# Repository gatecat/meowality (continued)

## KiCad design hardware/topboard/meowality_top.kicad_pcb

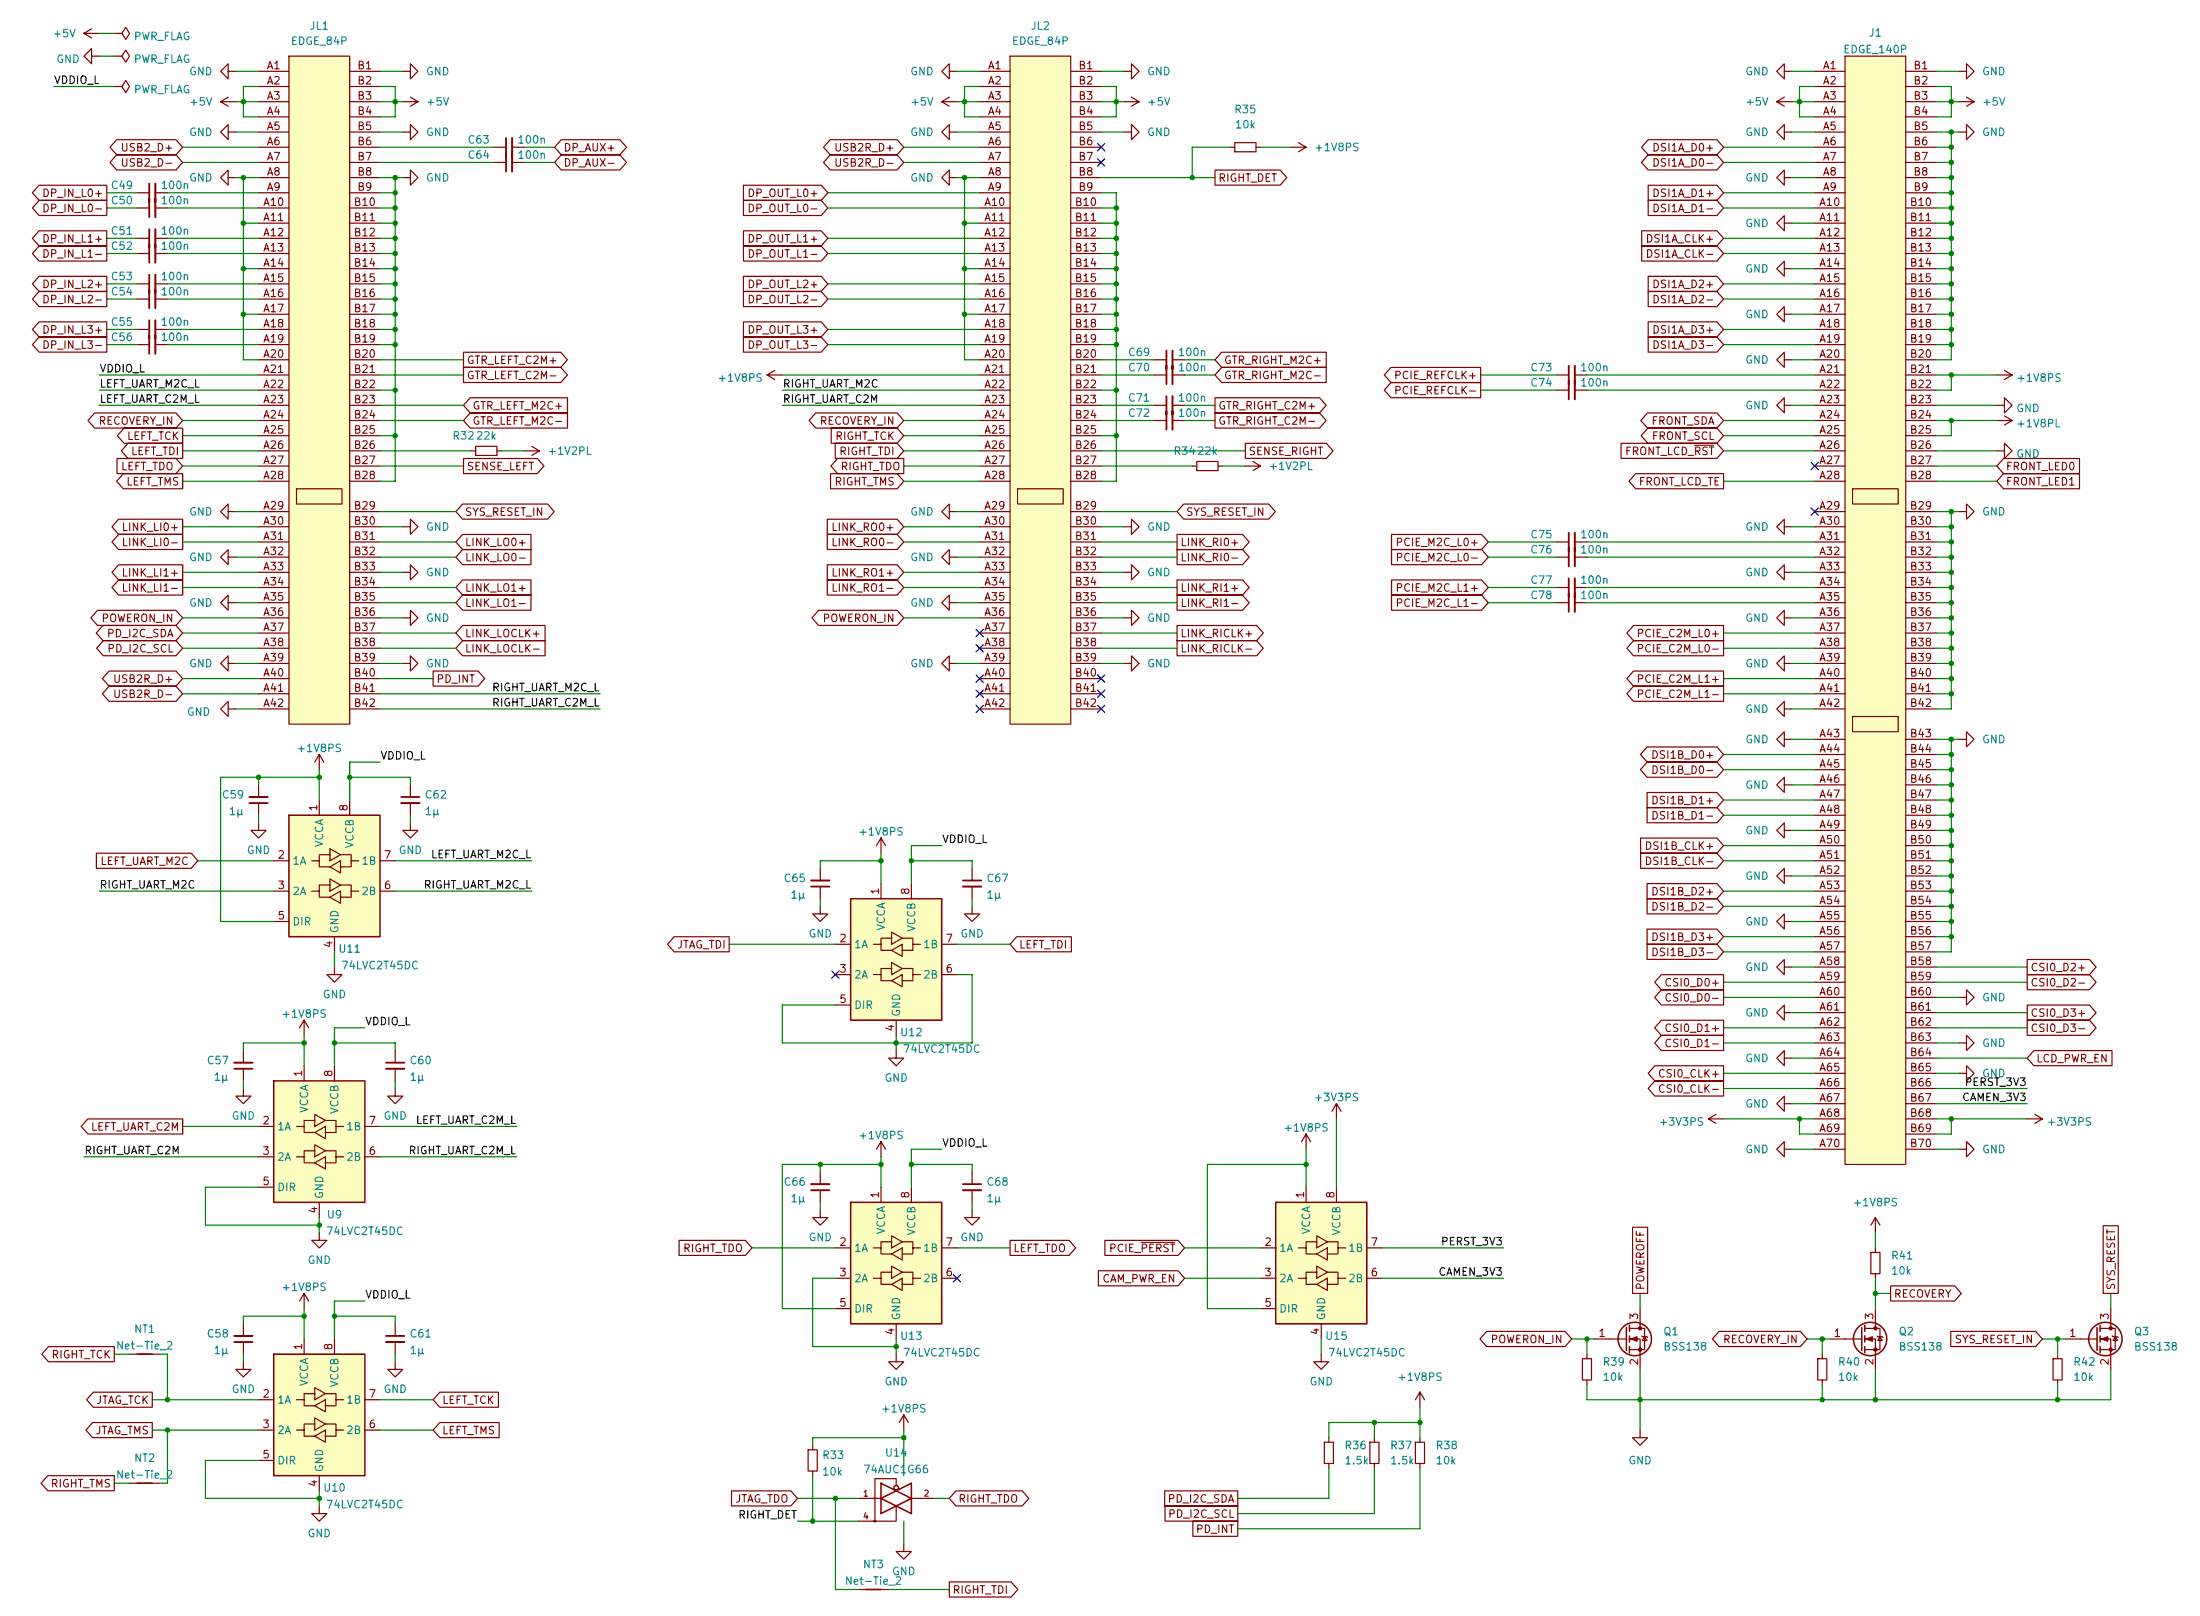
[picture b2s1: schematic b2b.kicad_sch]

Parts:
C49, C50, C51, C52, C53, C54, C55, C56, C63, C64, C69, C70, C71, C72, C73, C74, C75, C76, C77, C78: 100n; C_0402_1005Metric
C57, C58, C59, C60, C61, C62, C65, C66, C67, C68: 1µ; C_0603_1608Metric
J1: EDGE_140P; ME1014010101011
JL1: EDGE_84P; MET008431401101
JL2: EDGE_84P; EDGE_84P_0.6mm
NT1, NT2, NT3: Net-Tie_2; NetTie-2_SMD_Pad0.5mm
Q1, Q2, Q3: BSS138; SOT-23
R32, R34: 22k; R_0402_1005Metric
R33, R35, R38, R39, R40, R41, R42: 10k; R_0402_1005Metric
R36, R37: 1.5k; R_0402_1005Metric
U9, U10, U11, U12, U13, U15: 74LVC2T45DC; X2SON-8_1.4x1mm_P0.35mm
U14: 74AUC1G66; SOT-23-5

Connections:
+1V2PL: R32.2, R34.2; also elsewhere on the board
+1V8PL: J1.B24, J1.B25; also elsewhere on the board
+1V8PS: C57.2, C58.2, C59.2, C65.2, C66.2, J1.B21, J1.B22, JL2.A21, R33.1, R35.2, R36.1, R37.1, R38.1, R41.1, U9.1 (VCCA), U10.1 (VCCA), U11.1 (VCCA), U11.5 (DIR), U12.1 (VCCA), U13.1 (VCCA), U13.5 (DIR), U14.5 (VCC), U15.1 (VCCA), U15.5 (DIR); also elsewhere on the board
+3V3PS: J1.A68, J1.A69, J1.B68, J1.B69, U15.8 (VCCB); also elsewhere on the board
+5V: J1.A2, J1.A3, J1.A4, J1.B2, J1.B3, J1.B4, JL1.A2, JL1.A3, JL1.A4, JL1.B2, JL1.B3, JL1.B4, JL2.A2, JL2.A3, JL2.A4, JL2.B2, JL2.B3, JL2.B4; also elsewhere on the board
/B2B/CAMEN_3V3: J1.B67, U15.6 (2B)
/B2B/LEFT_UART_C2M_L: JL1.A23, U9.7 (1B)
/B2B/LEFT_UART_M2C_L: JL1.A22, U11.7 (1B)
/B2B/PERST_3V3: J1.B66, U15.7 (1B)
/B2B/RIGHT_UART_C2M: JL2.A23, U9.3 (2A)
/B2B/RIGHT_UART_C2M_L: JL1.B42, U9.6 (2B)
/B2B/RIGHT_UART_M2C: JL2.A22, U11.3 (2A)
/B2B/RIGHT_UART_M2C_L: JL1.B41, U11.6 (2B)
/B2B/VDDIO_L: C60.1, C61.1, C62.1, C67.1, C68.1, JL1.A21, U9.8 (VCCB), U10.8 (VCCB), U11.8 (VCCB), U12.8 (VCCB), U13.8 (VCCB)
CAM_PWR_EN: U15.3 (2A); also elsewhere on the board
CSI0_CLK+: J1.A65; also elsewhere on the board
CSI0_CLK-: J1.A66; also elsewhere on the board
CSI0_D0+: J1.A59; also elsewhere on the board
CSI0_D0-: J1.A60; also elsewhere on the board
CSI0_D1+: J1.A62; also elsewhere on the board
CSI0_D1-: J1.A63; also elsewhere on the board
CSI0_D2+: J1.B58; also elsewhere on the board
CSI0_D2-: J1.B59; also elsewhere on the board
CSI0_D3+: J1.B61; also elsewhere on the board
CSI0_D3-: J1.B62; also elsewhere on the board
DP_AUX+: C63.2; also elsewhere on the board
DP_AUX-: C64.2; also elsewhere on the board
DP_IN_L0+: C49.1; also elsewhere on the board
DP_IN_L0-: C50.1; also elsewhere on the board
DP_IN_L1+: C51.1; also elsewhere on the board
DP_IN_L1-: C52.1; also elsewhere on the board
DP_IN_L2+: C53.1; also elsewhere on the board
DP_IN_L2-: C54.1; also elsewhere on the board
DP_IN_L3+: C55.1; also elsewhere on the board
DP_IN_L3-: C56.1; also elsewhere on the board
DP_OUT_L0+: JL2.A9; also elsewhere on the board
DP_OUT_L0-: JL2.A10; also elsewhere on the board
DP_OUT_L1+: JL2.A12; also elsewhere on the board
DP_OUT_L1-: JL2.A13; also elsewhere on the board
DP_OUT_L2+: JL2.A15; also elsewhere on the board
DP_OUT_L2-: JL2.A16; also elsewhere on the board
DP_OUT_L3+: JL2.A18; also elsewhere on the board
DP_OUT_L3-: JL2.A19; also elsewhere on the board
DSI1A_CLK+: J1.A12; also elsewhere on the board
DSI1A_CLK-: J1.A13; also elsewhere on the board
DSI1A_D0+: J1.A6; also elsewhere on the board
DSI1A_D0-: J1.A7; also elsewhere on the board
DSI1A_D1+: J1.A9; also elsewhere on the board
DSI1A_D1-: J1.A10; also elsewhere on the board
DSI1A_D2+: J1.A15; also elsewhere on the board
DSI1A_D2-: J1.A16; also elsewhere on the board
DSI1A_D3+: J1.A18; also elsewhere on the board
DSI1A_D3-: J1.A19; also elsewhere on the board
DSI1B_CLK+: J1.A50; also elsewhere on the board
DSI1B_CLK-: J1.A51; also elsewhere on the board
DSI1B_D0+: J1.A44; also elsewhere on the board
DSI1B_D0-: J1.A45; also elsewhere on the board
DSI1B_D1+: J1.A47; also elsewhere on the board
DSI1B_D1-: J1.A48; also elsewhere on the board
DSI1B_D2+: J1.A53; also elsewhere on the board
DSI1B_D2-: J1.A54; also elsewhere on the board
DSI1B_D3+: J1.A56; also elsewhere on the board
DSI1B_D3-: J1.A57; also elsewhere on the board
FRONT_LCD_TE: J1.A28; also elsewhere on the board
FRONT_LCD_~RST: J1.A26; also elsewhere on the board
FRONT_LED0: J1.B27; also elsewhere on the board
FRONT_LED1: J1.B28; also elsewhere on the board
FRONT_SCL: J1.A25; also elsewhere on the board
FRONT_SDA: J1.A24; also elsewhere on the board
GND: C57.1, C58.1, C59.1, C60.2, C61.2, C62.2, C65.1, C66.1, C67.2, C68.2, J1.A1, J1.A5, J1.A8, J1.A11, J1.A14, J1.A17, J1.A20, J1.A23, J1.A30, J1.A33, J1.A36, J1.A39, J1.A42, J1.A43, J1.A46, J1.A49, J1.A52, J1.A55, J1.A58, J1.A61, J1.A64, J1.A67, J1.A70, J1.B1, J1.B5, J1.B6, J1.B7, J1.B8, J1.B9, J1.B10, J1.B11, J1.B12, J1.B13, J1.B14, J1.B15, J1.B16, J1.B17, J1.B18, J1.B19, J1.B20, J1.B23, J1.B26, J1.B29, J1.B30, J1.B31, J1.B32, J1.B33, J1.B34, J1.B35, J1.B36, J1.B37, J1.B38, J1.B39, J1.B40, J1.B41, J1.B42, J1.B43, J1.B44, J1.B45, J1.B46, J1.B47, J1.B48, J1.B49, J1.B50, J1.B51, J1.B52, J1.B53, J1.B54, J1.B55, J1.B56, J1.B57, J1.B60, J1.B63, J1.B65, J1.B70, JL1.A1, JL1.A5, JL1.A8, JL1.A11, JL1.A14, JL1.A17, JL1.A20, JL1.A29, JL1.A32, JL1.A35, JL1.A39, JL1.A42, JL1.B1, JL1.B5, JL1.B8, JL1.B9, JL1.B10, JL1.B11, JL1.B12, JL1.B13, JL1.B14, JL1.B15, JL1.B16, JL1.B17, JL1.B18, JL1.B19, JL1.B22, JL1.B25, JL1.B28, JL1.B30, JL1.B33, JL1.B36, JL1.B39, JL2.A1, JL2.A5, JL2.A8, JL2.A11, JL2.A14, JL2.A17, JL2.A20, JL2.A29, JL2.A32, JL2.A35, JL2.A39, JL2.B1, JL2.B5, JL2.B30, JL2.B33, JL2.B36, JL2.B39, Q1.2 (S), Q2.2 (S), Q3.2 (S), R39.2, R40.2, R42.2, U9.4 (GND), U9.5 (DIR), U10.4 (GND), U10.5 (DIR), U11.4 (GND), U12.4 (GND), U12.5 (DIR), U12.6 (2B), U13.3 (2A), U13.4 (GND), U14.3 (GND), U15.4 (GND); also elsewhere on the board
GTR_LEFT_C2M+: JL1.B20; also elsewhere on the board
GTR_LEFT_C2M-: JL1.B21; also elsewhere on the board
GTR_LEFT_M2C+: JL1.B23; also elsewhere on the board
GTR_LEFT_M2C-: JL1.B24; also elsewhere on the board
GTR_RIGHT_C2M+: C71.2; also elsewhere on the board
GTR_RIGHT_C2M-: C72.2; also elsewhere on the board
GTR_RIGHT_M2C+: C69.2; also elsewhere on the board
GTR_RIGHT_M2C-: C70.2; also elsewhere on the board
JTAG_TCK: NT1.2, U10.2 (1A); also elsewhere on the board
JTAG_TDI: U12.2 (1A); also elsewhere on the board
JTAG_TDO: NT3.1, U14.1
JTAG_TMS: NT2.2, U10.3 (2A); also elsewhere on the board
LCD_PWR_EN: J1.B64; also elsewhere on the board
LEFT_TCK: JL1.A25, U10.7 (1B)
LEFT_TDI: JL1.A26, U12.7 (1B)
LEFT_TDO: JL1.A27, U13.7 (1B)
LEFT_TMS: JL1.A28, U10.6 (2B)
LEFT_UART_C2M: U9.2 (1A); also elsewhere on the board
LEFT_UART_M2C: U11.2 (1A); also elsewhere on the board
LINK_LI0+: JL1.A30; also elsewhere on the board
LINK_LI0-: JL1.A31; also elsewhere on the board
LINK_LI1+: JL1.A33; also elsewhere on the board
LINK_LI1-: JL1.A34; also elsewhere on the board
LINK_LO0+: JL1.B31; also elsewhere on the board
LINK_LO0-: JL1.B32; also elsewhere on the board
LINK_LO1+: JL1.B34; also elsewhere on the board
LINK_LO1-: JL1.B35; also elsewhere on the board
LINK_LOCLK+: JL1.B37; also elsewhere on the board
LINK_LOCLK-: JL1.B38; also elsewhere on the board
LINK_RI0+: JL2.B31; also elsewhere on the board
LINK_RI0-: JL2.B32; also elsewhere on the board
LINK_RI1+: JL2.B34; also elsewhere on the board
LINK_RI1-: JL2.B35; also elsewhere on the board
LINK_RICLK+: JL2.B37; also elsewhere on the board
LINK_RICLK-: JL2.B38; also elsewhere on the board
LINK_RO0+: JL2.A30; also elsewhere on the board
LINK_RO0-: JL2.A31; also elsewhere on the board
LINK_RO1+: JL2.A33; also elsewhere on the board
LINK_RO1-: JL2.A34; also elsewhere on the board
unnamed: C49.2, JL1.A9
unnamed: C50.2, JL1.A10
unnamed: C51.2, JL1.A12
unnamed: C52.2, JL1.A13
unnamed: C53.2, JL1.A15
unnamed: C54.2, JL1.A16
unnamed: C55.2, JL1.A18
unnamed: C56.2, JL1.A19
unnamed: C63.1, JL1.B6
unnamed: C64.1, JL1.B7
unnamed: C69.1, JL2.B20
unnamed: C70.1, JL2.B21
unnamed: C71.1, JL2.B23
unnamed: C72.1, JL2.B24
unnamed: C73.2, J1.A21
unnamed: C74.2, J1.A22
unnamed: C75.2, J1.A31
unnamed: C76.2, J1.A32
unnamed: C77.2, J1.A34
unnamed: C78.2, J1.A35
unnamed: JL1.B26, R32.1
unnamed: JL2.B9, JL2.B10, JL2.B11, JL2.B12, JL2.B13, JL2.B14, JL2.B15, JL2.B16, JL2.B17, JL2.B18, JL2.B19, JL2.B22, JL2.B25, JL2.B28
unnamed: JL2.B27, R34.1
PCIE_C2M_L0+: J1.A37; also elsewhere on the board
PCIE_C2M_L0-: J1.A38; also elsewhere on the board
PCIE_C2M_L1+: J1.A40; also elsewhere on the board
PCIE_C2M_L1-: J1.A41; also elsewhere on the board
PCIE_M2C_L0+: C75.1; also elsewhere on the board
PCIE_M2C_L0-: C76.1; also elsewhere on the board
PCIE_M2C_L1+: C77.1; also elsewhere on the board
PCIE_M2C_L1-: C78.1; also elsewhere on the board
PCIE_REFCLK+: C73.1; also elsewhere on the board
PCIE_REFCLK-: C74.1; also elsewhere on the board
PCIE_~PERST: U15.2 (1A); also elsewhere on the board
PD_I2C_SCL: JL1.A38, R37.2; also elsewhere on the board
PD_I2C_SDA: JL1.A37, R36.2; also elsewhere on the board
PD_INT: JL1.B40, R38.2; also elsewhere on the board
POWEROFF: Q1.3 (D); also elsewhere on the board
POWERON_IN: JL1.A36, JL2.A36, Q1.1 (G), R39.1
RECOVERY: Q2.3 (D), R41.2; also elsewhere on the board
RECOVERY_IN: JL1.A24, JL2.A24, Q2.1 (G), R40.1
RIGHT_DET: JL2.B8, R33.2, R35.1, U14.4; also elsewhere on the board
RIGHT_TCK: JL2.A25, NT1.1
RIGHT_TDI: JL2.A26, NT3.2
RIGHT_TDO: JL2.A27, U13.2 (1A), U14.2
RIGHT_TMS: JL2.A28, NT2.1
SENSE_LEFT: JL1.B27; also elsewhere on the board
SENSE_RIGHT: JL2.B26; also elsewhere on the board
SYS_RESET: Q3.3 (D); also elsewhere on the board
SYS_RESET_IN: JL1.B29, JL2.B29, Q3.1 (G), R42.1
USB2R_D+: JL1.A40, JL2.A6
USB2R_D-: JL1.A41, JL2.A7
USB2_D+: JL1.A6; also elsewhere on the board
USB2_D-: JL1.A7; also elsewhere on the board

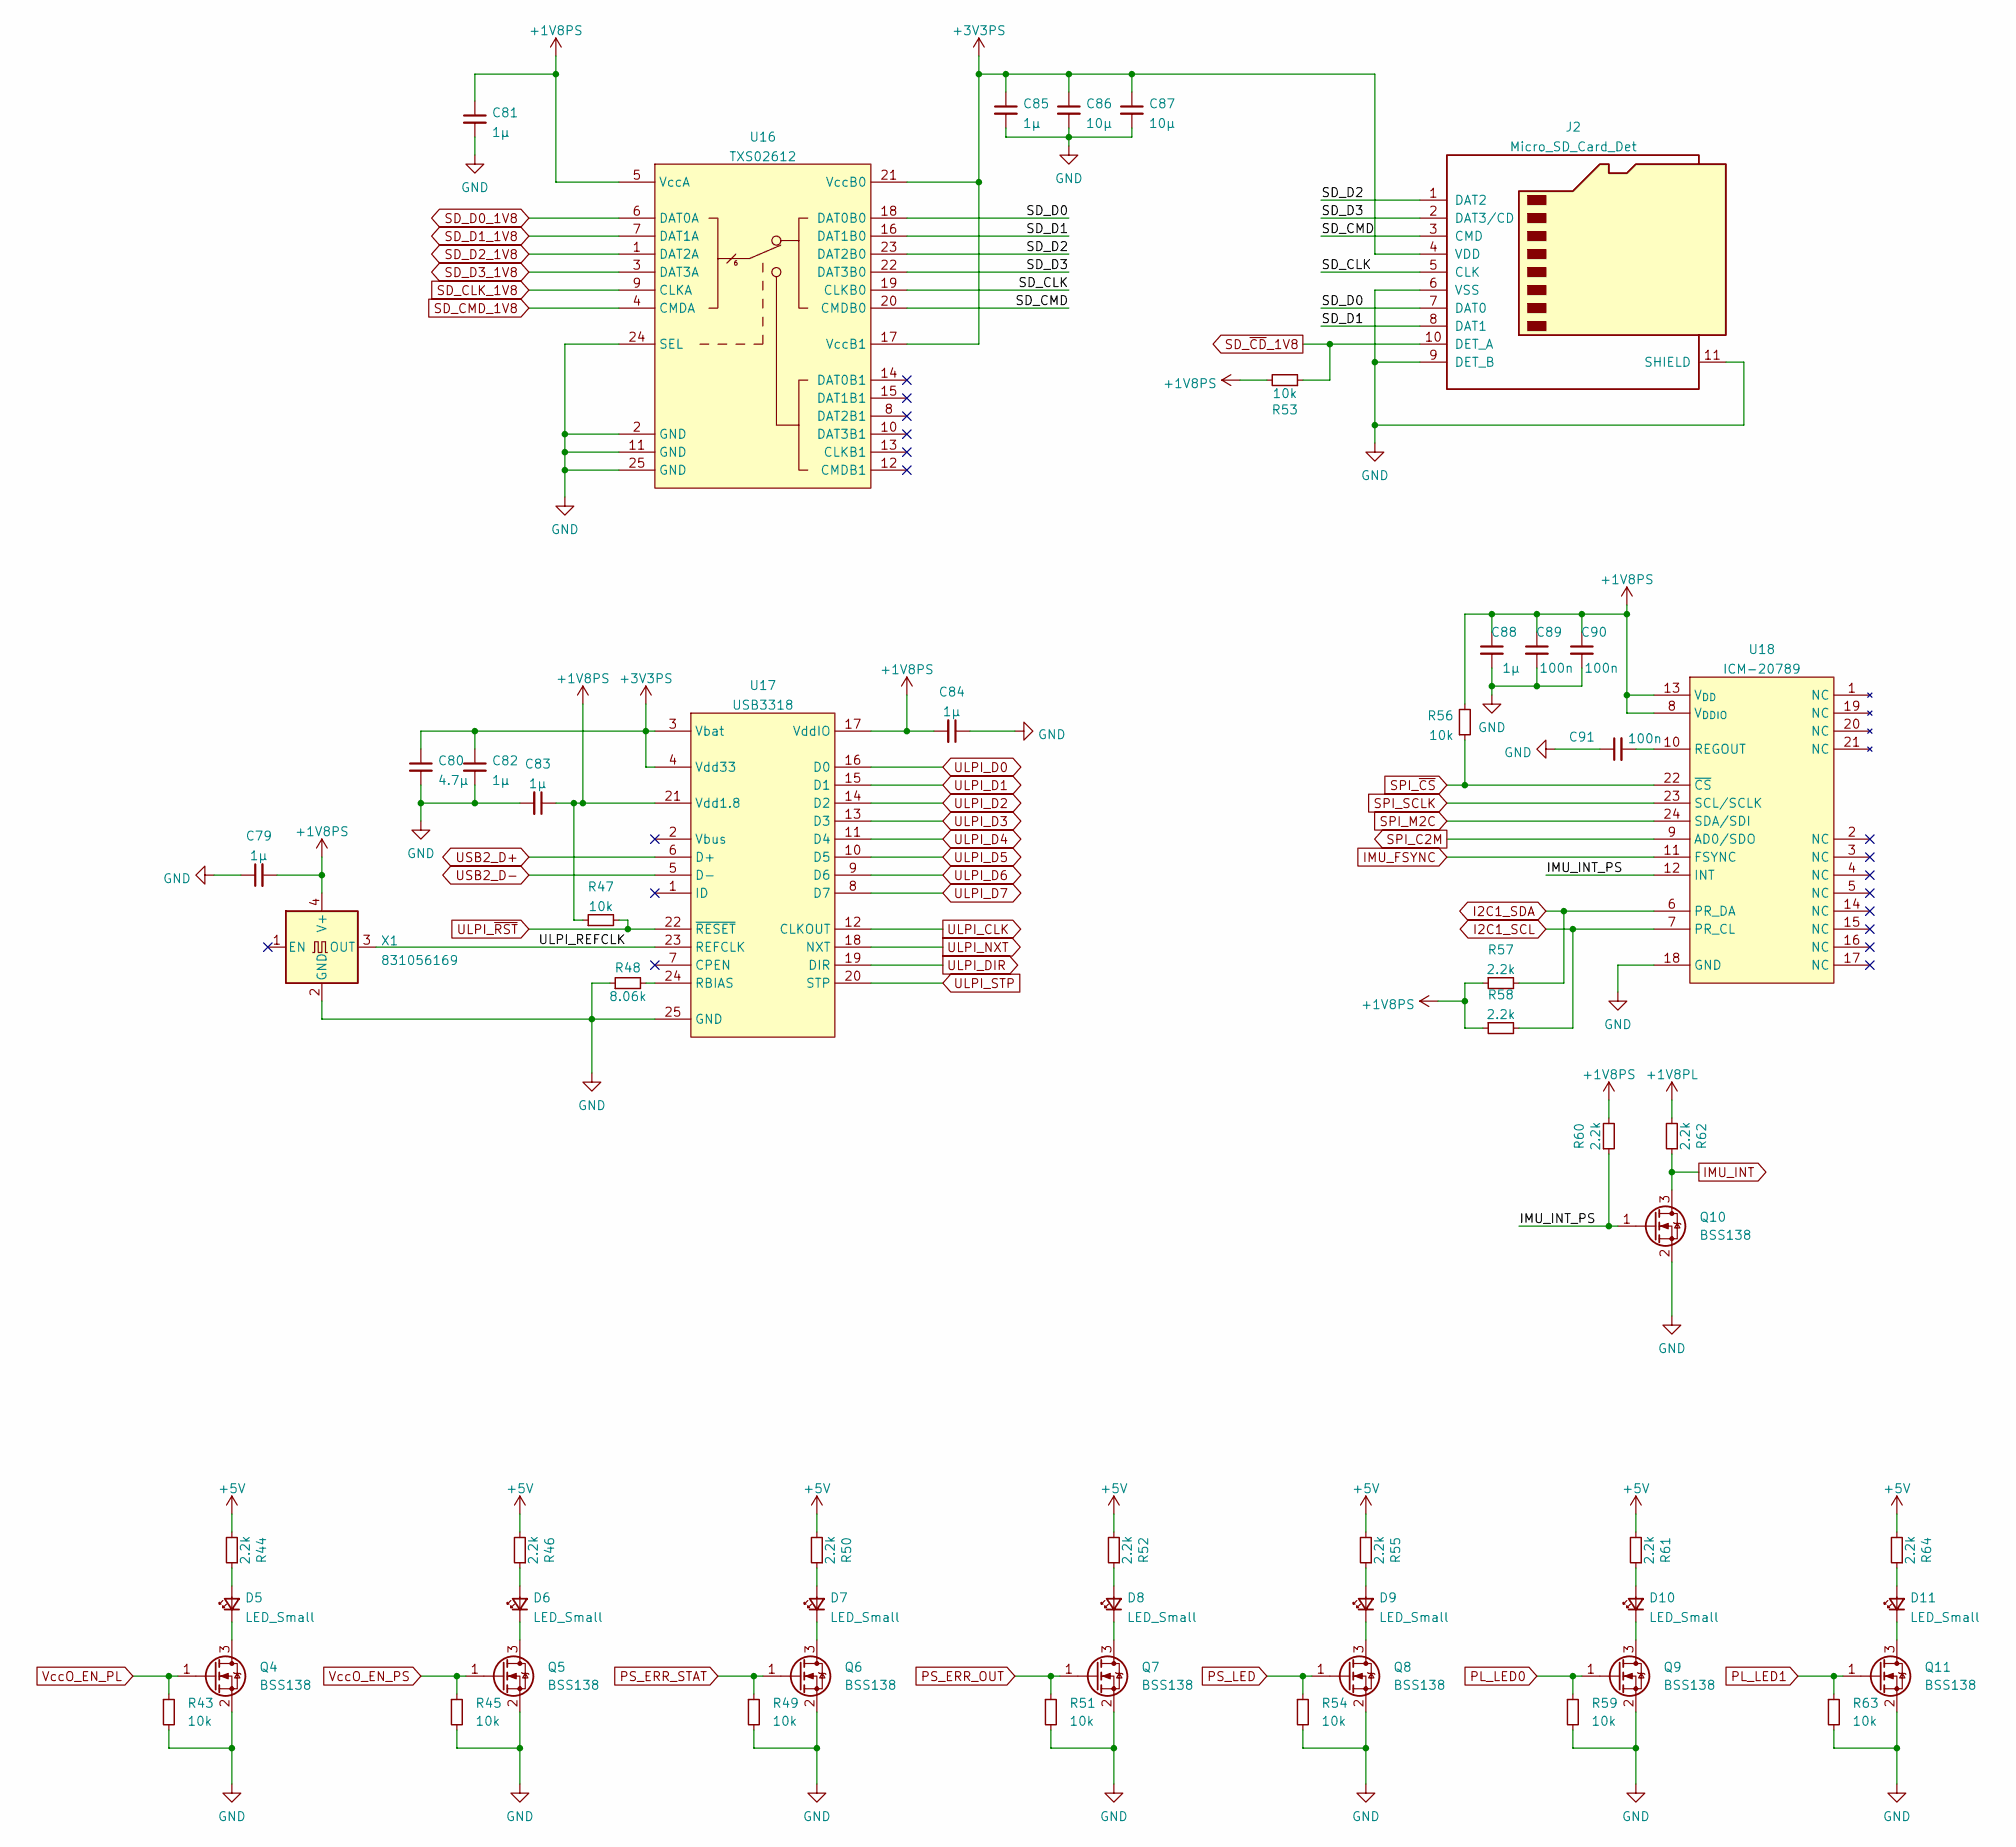
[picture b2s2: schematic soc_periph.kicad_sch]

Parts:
C79, C81, C82, C83, C84, C85, C88: 1µ; C_0603_1608Metric
C80: 4.7µ; C_0805_2012Metric_Pad1.15x1.40mm_HandSolder
C86, C87: 10µ; C_0805_2012Metric
C89, C90, C91: 100n; C_0402_1005Metric
D5, D6, D7, D8, D9, D10, D11: LED_Small; LED_0603_1608Metric
J2: Micro_SD_Card_Det; microSD_HC_Hirose_DM3AT-SF-PEJM5
Q4, Q5, Q6, Q7, Q8, Q9, Q10, Q11: BSS138; SOT-23
R43, R45, R47, R49, R51, R53, R54, R56, R59, R63: 10k; R_0402_1005Metric
R44, R46, R50, R52, R55, R57, R58, R60, R61, R62, R64: 2.2k; R_0402_1005Metric
R48: 8.06k; R_0402_1005Metric
U16: TXS02612; WQFN-24-1EP_4x4mm_P0.5mm_EP2.45x2.45mm
U17: USB3318; HVQFN-24-1EP_4x4mm_P0.5mm_EP2.5x2.5mm
U18: ICM-20789
X1: 831056169; Oscillator_SMD_EuroQuartz_XO32-4Pin_3.2x2.5mm

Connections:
+1V8PL: R62.2; also elsewhere on the board
+1V8PS: C79.2, C81.1, C83.1, C84.2, C88.1, C89.1, C90.1, R47.1, R53.2, R56.2, R57.1, R58.1, R60.2, U16.5 (VccA), U17.17 (VddIO), U17.21 (Vdd1.8), U18.8 (V_{DDIO}), U18.13 (V_{DD}), X1.4 (V+); also elsewhere on the board
+3V3PS: C80.1, C82.1, C85.1, C86.1, C87.1, J2.4 (VDD), U16.17 (VccB1), U16.21 (VccB0), U17.3 (Vbat), U17.4 (Vdd33); also elsewhere on the board
+5V: R44.2, R46.2, R50.2, R52.2, R55.2, R61.2, R64.2; also elsewhere on the board
/Periph/IMU_INT_PS: Q10.1 (G), R60.1, U18.12 (INT)
/Periph/SD_CLK: J2.5 (CLK), U16.19 (CLKB0)
/Periph/SD_CMD: J2.3 (CMD), U16.20 (CMDB0)
/Periph/SD_D0: J2.7 (DAT0), U16.18 (DAT0B0)
/Periph/SD_D1: J2.8 (DAT1), U16.16 (DAT1B0)
/Periph/SD_D2: J2.1 (DAT2), U16.23 (DAT2B0)
/Periph/SD_D3: J2.2 (DAT3/CD), U16.22 (DAT3B0)
/Periph/ULPI_REFCLK: U17.23 (REFCLK), X1.3 (OUT)
GND: C79.1, C80.2, C81.2, C82.2, C83.2, C84.1, C85.2, C86.2, C87.2, C88.2, C89.2, C90.2, C91.1, J2.6 (VSS), J2.9 (DET_B), J2.11 (SHIELD), Q4.2 (S), Q5.2 (S), Q6.2 (S), Q7.2 (S), Q8.2 (S), Q9.2 (S), Q10.2 (S), Q11.2 (S), R43.2, R45.2, R48.1, R49.2, R51.2, R54.2, R59.2, R63.2, U16.2 (GND), U16.11 (GND), U16.24 (SEL), U16.25 (GND), U17.25 (GND), U18.18 (GND), X1.2 (GND); also elsewhere on the board
I2C1_SCL: R58.2, U18.7 (PR_CL); also elsewhere on the board
I2C1_SDA: R57.2, U18.6 (PR_DA); also elsewhere on the board
IMU_INT: Q10.3 (D), R62.1; also elsewhere on the board
unnamed: C91.2, U18.10 (REGOUT)
unnamed: D5.1 (K), Q4.3 (D)
unnamed: D5.2 (A), R44.1
unnamed: D6.1 (K), Q5.3 (D)
unnamed: D6.2 (A), R46.1
unnamed: D7.1 (K), Q6.3 (D)
unnamed: D7.2 (A), R50.1
unnamed: D8.1 (K), Q7.3 (D)
unnamed: D8.2 (A), R52.1
unnamed: D9.1 (K), Q8.3 (D)
unnamed: D9.2 (A), R55.1
unnamed: D10.1 (K), Q9.3 (D)
unnamed: D10.2 (A), R61.1
unnamed: D11.1 (K), Q11.3 (D)
unnamed: D11.2 (A), R64.1
unnamed: R48.2, U17.24 (RBIAS)
PL_LED0: Q9.1 (G), R59.1; also elsewhere on the board
PL_LED1: Q11.1 (G), R63.1; also elsewhere on the board
PS_ERR_OUT: Q7.1 (G), R51.1; also elsewhere on the board
PS_ERR_STAT: Q6.1 (G), R49.1; also elsewhere on the board
PS_LED: Q8.1 (G), R54.1; also elsewhere on the board
SD_CLK_1V8: U16.9 (CLKA); also elsewhere on the board
SD_CMD_1V8: U16.4 (CMDA); also elsewhere on the board
SD_D0_1V8: U16.6 (DAT0A); also elsewhere on the board
SD_D1_1V8: U16.7 (DAT1A); also elsewhere on the board
SD_D2_1V8: U16.1 (DAT2A); also elsewhere on the board
SD_D3_1V8: U16.3 (DAT3A); also elsewhere on the board
SD_~CD_1V8: J2.10 (DET_A), R53.1; also elsewhere on the board
SPI_~CS: R56.1, U18.22 (~CS); also elsewhere on the board
ULPI_CLK: U17.12 (CLKOUT); also elsewhere on the board
ULPI_D0: U17.16 (D0); also elsewhere on the board
ULPI_D1: U17.15 (D1); also elsewhere on the board
ULPI_D2: U17.14 (D2); also elsewhere on the board
ULPI_D3: U17.13 (D3); also elsewhere on the board
ULPI_D4: U17.11 (D4); also elsewhere on the board
ULPI_D5: U17.10 (D5); also elsewhere on the board
ULPI_D6: U17.9 (D6); also elsewhere on the board
ULPI_D7: U17.8 (D7); also elsewhere on the board
ULPI_DIR: U17.19 (DIR); also elsewhere on the board
ULPI_NXT: U17.18 (NXT); also elsewhere on the board
ULPI_STP: U17.20 (STP); also elsewhere on the board
ULPI_~RST: R47.2, U17.22 (~RESET); also elsewhere on the board
USB2_D+: U17.6 (D+); also elsewhere on the board
USB2_D-: U17.5 (D-); also elsewhere on the board
VccO_EN_PL: Q4.1 (G), R43.1; also elsewhere on the board
VccO_EN_PS: Q5.1 (G), R45.1; also elsewhere on the board

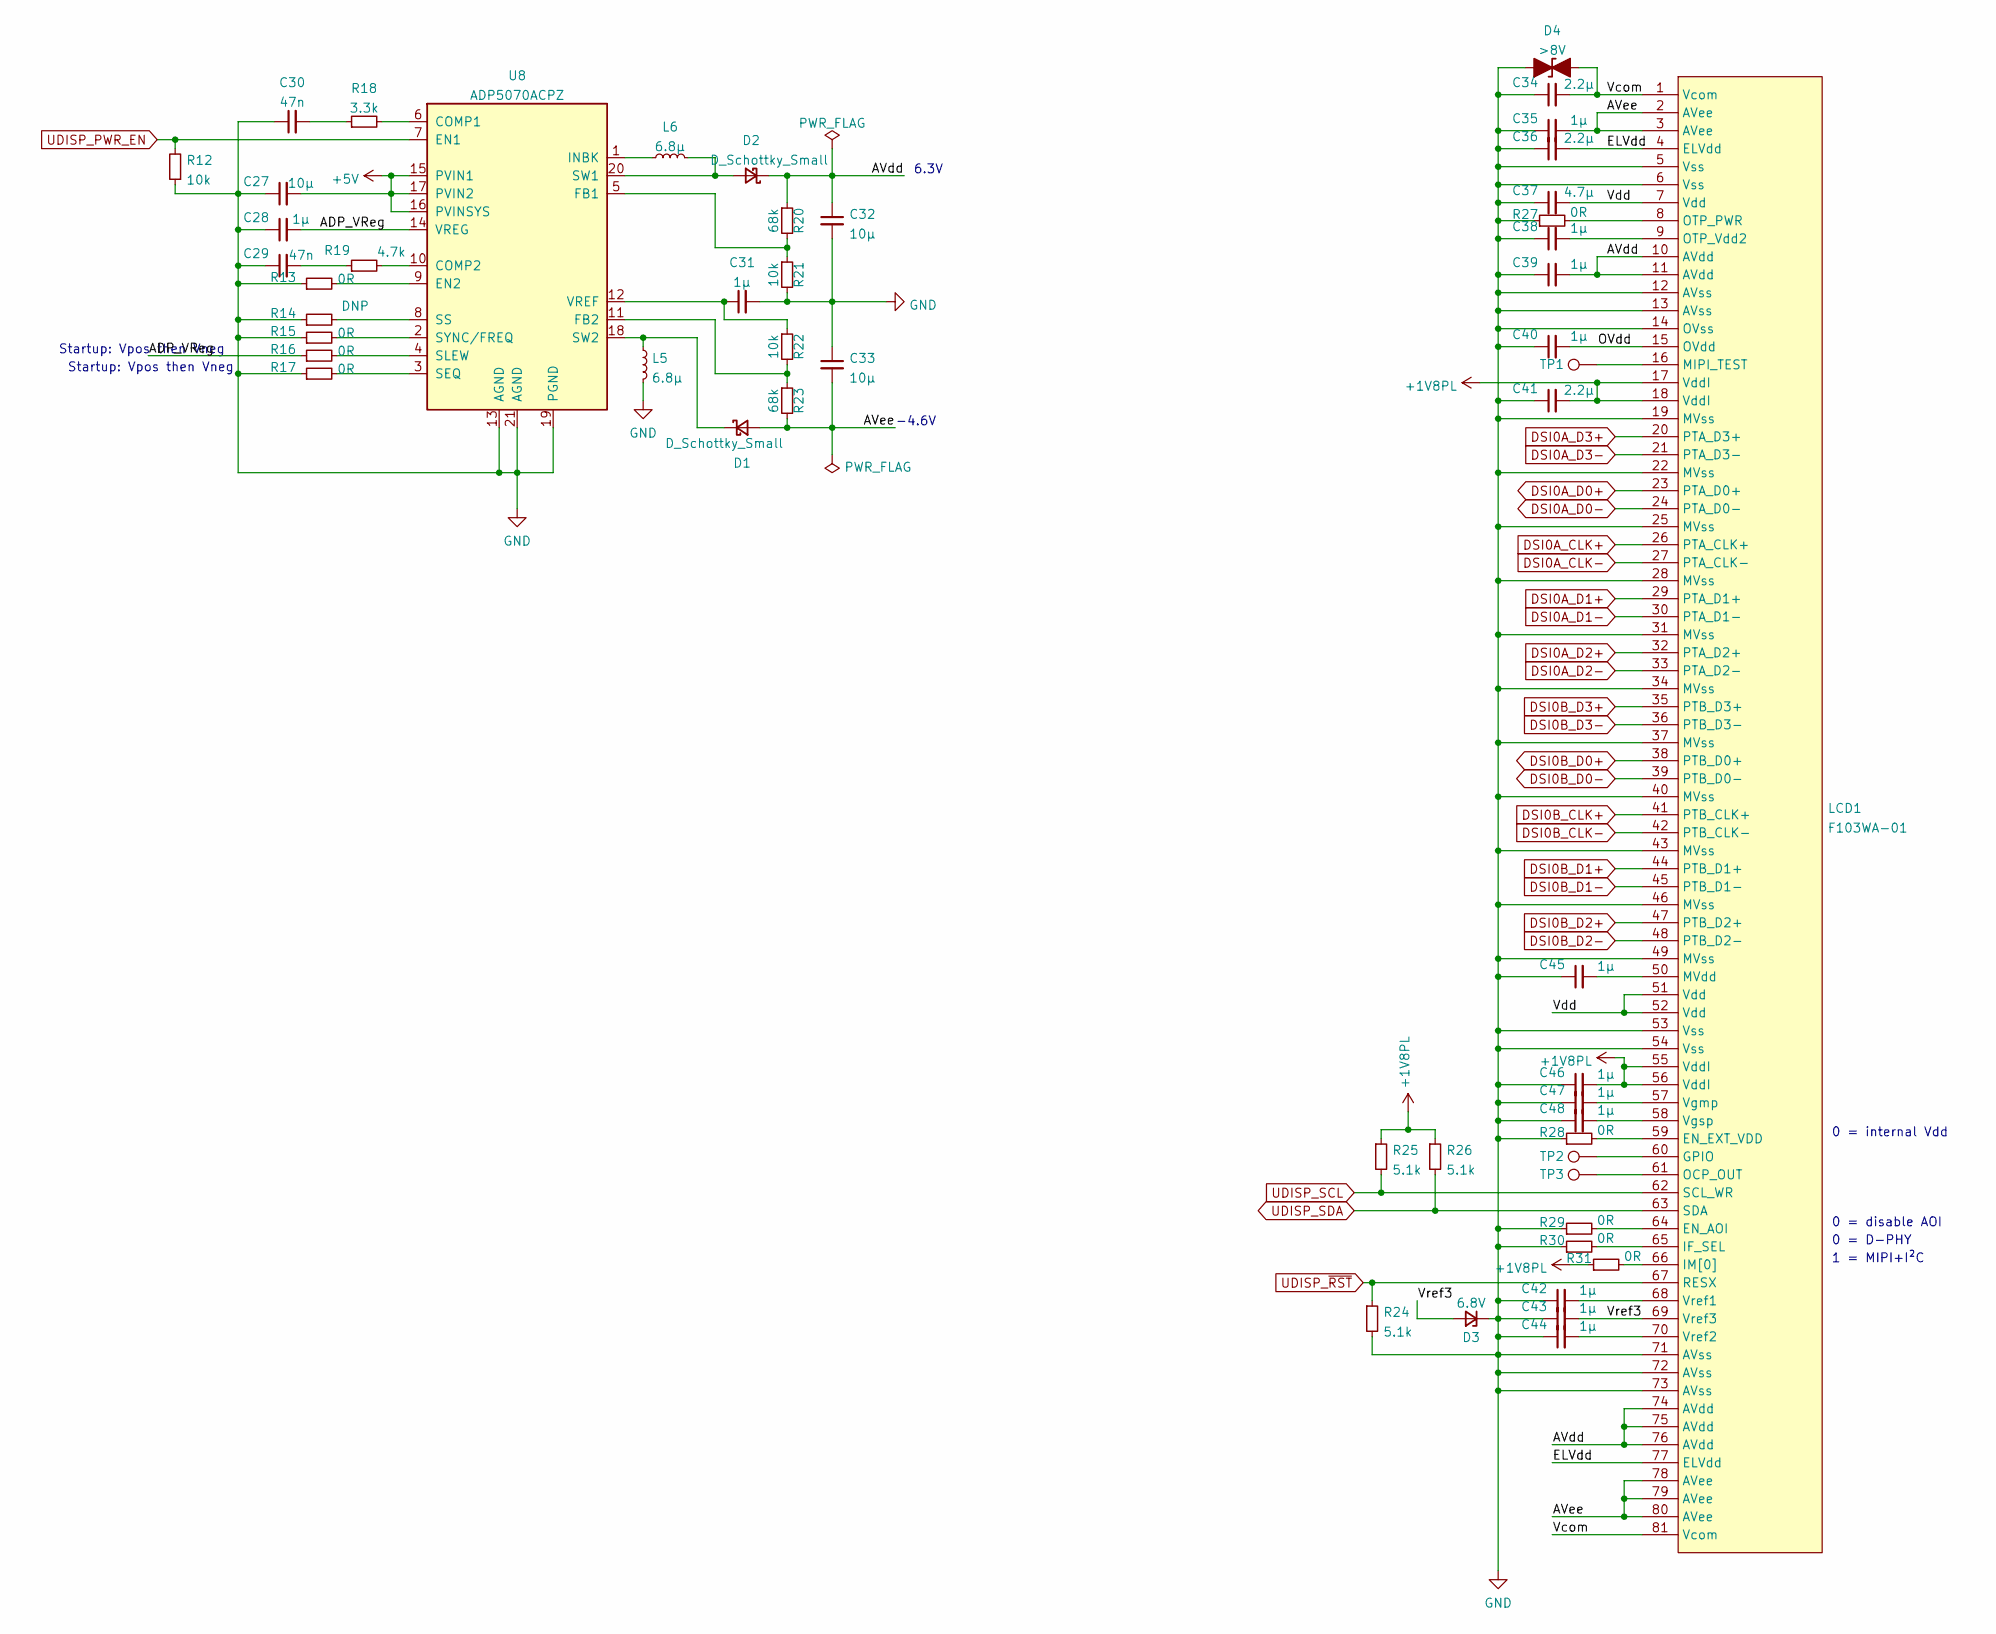
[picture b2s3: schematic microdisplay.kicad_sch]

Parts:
C27, C32, C33: 10µ; C_0805_2012Metric
C28, C31, C35, C38, C39, C40, C42, C43, C44, C45, C46, C47, C48: 1µ; C_0603_1608Metric
C29, C30: 47n; C_0402_1005Metric
C34, C36, C41: 2.2µ; C_0603_1608Metric
C37: 4.7µ; C_0805_2012Metric
D1, D2: D_Schottky_Small; D_SMA
D3: 6.8V; D_SMA
D4: >8V; D_SMA
L5, L6: 6.8µ; L_Taiyo-Yuden_NR-50xx
LCD1: F103WA-01; FF0881SA1
R12, R21, R22: 10k; R_0402_1005Metric
R13, R15, R16, R17, R27, R28, R29, R30, R31: 0R; R_0402_1005Metric
R14: DNP; R_0402_1005Metric
R18: 3.3k; R_0402_1005Metric
R19: 4.7k; R_0402_1005Metric
R20, R23: 68k; R_0402_1005Metric
R24, R25, R26: 5.1k; R_0402_1005Metric
TP1, TP2, TP3: TestPoint_Pad_D1.5mm
U8: ADP5070ACPZ; QFN-20-1EP_4x4mm_P0.5mm_EP2.6x2.6mm

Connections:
+1V8PL: C41.2, C46.2, LCD1.17 (VddI), LCD1.18 (VddI), LCD1.55 (VddI), LCD1.56 (VddI), R25.1, R26.1, R31.1; also elsewhere on the board
+5V: C27.2, U8.15 (PVIN1), U8.16 (PVINSYS), U8.17 (PVIN2); also elsewhere on the board
/Microdisplay/ADP_VReg: C28.2, R16.1, U8.14 (VREG)
/Microdisplay/AVdd: C32.1, C39.2, D2.1 (K), LCD1.10 (AVdd), LCD1.11 (AVdd), LCD1.74 (AVdd), LCD1.75 (AVdd), LCD1.76 (AVdd), R20.1
/Microdisplay/AVee: C33.2, C35.2, D1.2 (A), LCD1.2 (AVee), LCD1.3 (AVee), LCD1.78 (AVee), LCD1.79 (AVee), LCD1.80 (AVee), R23.2
/Microdisplay/ELVdd: C36.2, LCD1.4 (ELVdd), LCD1.77 (ELVdd)
/Microdisplay/OVdd: C40.2, LCD1.15 (OVdd)
/Microdisplay/Vcom: C34.2, D4.2 (A2), LCD1.1 (Vcom), LCD1.81 (Vcom)
/Microdisplay/Vdd: C37.2, LCD1.7 (Vdd), LCD1.51 (Vdd), LCD1.52 (Vdd)
/Microdisplay/Vref3: C43.2, D3.2 (A), LCD1.69 (Vref3)
DSI0A_CLK+: LCD1.26 (PTA_CLK+); also elsewhere on the board
DSI0A_CLK-: LCD1.27 (PTA_CLK-); also elsewhere on the board
DSI0A_D0+: LCD1.23 (PTA_D0+); also elsewhere on the board
DSI0A_D0-: LCD1.24 (PTA_D0-); also elsewhere on the board
DSI0A_D1+: LCD1.29 (PTA_D1+); also elsewhere on the board
DSI0A_D1-: LCD1.30 (PTA_D1-); also elsewhere on the board
DSI0A_D2+: LCD1.32 (PTA_D2+); also elsewhere on the board
DSI0A_D2-: LCD1.33 (PTA_D2-); also elsewhere on the board
DSI0A_D3+: LCD1.20 (PTA_D3+); also elsewhere on the board
DSI0A_D3-: LCD1.21 (PTA_D3-); also elsewhere on the board
DSI0B_CLK+: LCD1.41 (PTB_CLK+); also elsewhere on the board
DSI0B_CLK-: LCD1.42 (PTB_CLK-); also elsewhere on the board
DSI0B_D0+: LCD1.38 (PTB_D0+); also elsewhere on the board
DSI0B_D0-: LCD1.39 (PTB_D0-); also elsewhere on the board
DSI0B_D1+: LCD1.44 (PTB_D1+); also elsewhere on the board
DSI0B_D1-: LCD1.45 (PTB_D1-); also elsewhere on the board
DSI0B_D2+: LCD1.47 (PTB_D2+); also elsewhere on the board
DSI0B_D2-: LCD1.48 (PTB_D2-); also elsewhere on the board
DSI0B_D3+: LCD1.35 (PTB_D3+); also elsewhere on the board
DSI0B_D3-: LCD1.36 (PTB_D3-); also elsewhere on the board
GND: C27.1, C28.1, C29.1, C30.1, C31.2, C32.2, C33.1, C34.1, C35.1, C36.1, C37.1, C38.1, C39.1, C40.1, C41.1, C42.1, C43.1, C44.1, C45.1, C46.1, C47.1, C48.1, D3.1 (K), D4.1 (A1), L5.2, LCD1.5 (Vss), LCD1.6 (Vss), LCD1.12 (AVss), LCD1.13 (AVss), LCD1.14 (OVss), LCD1.19 (MVss), LCD1.22 (MVss), LCD1.25 (MVss), LCD1.28 (MVss), LCD1.31 (MVss), LCD1.34 (MVss), LCD1.37 (MVss), LCD1.40 (MVss), LCD1.43 (MVss), LCD1.46 (MVss), LCD1.49 (MVss), LCD1.53 (Vss), LCD1.54 (Vss), LCD1.71 (AVss), LCD1.72 (AVss), LCD1.73 (AVss), R12.1, R13.1, R14.1, R15.1, R17.1, R21.2, R24.2, R27.1, R28.1, R29.1, R30.1, U8.13 (AGND), U8.19 (PGND), U8.21 (AGND); also elsewhere on the board
unnamed: C29.2, R19.1
unnamed: C30.2, R18.1
unnamed: C31.1, R22.1, U8.12 (VREF)
unnamed: C38.2, LCD1.9 (OTP_Vdd2)
unnamed: C42.2, LCD1.68 (Vref1)
unnamed: C44.2, LCD1.70 (Vref2)
unnamed: C45.2, LCD1.50 (MVdd)
unnamed: C47.2, LCD1.57 (Vgmp)
unnamed: C48.2, LCD1.58 (Vgsp)
unnamed: D1.1 (K), L5.1, U8.18 (SW2)
unnamed: D2.2 (A), L6.2, U8.20 (SW1)
unnamed: L6.1, U8.1 (INBK)
unnamed: LCD1.8 (OTP_PWR), R27.2
unnamed: LCD1.16 (MIPI_TEST), TP1.1
unnamed: LCD1.59 (EN_EXT_VDD), R28.2
unnamed: LCD1.60 (GPIO), TP2.1
unnamed: LCD1.61 (OCP_OUT), TP3.1
unnamed: LCD1.64 (EN_AOI), R29.2
unnamed: LCD1.65 (IF_SEL), R30.2
unnamed: LCD1.66 (IM[0]), R31.2
unnamed: R13.2, U8.9 (EN2)
unnamed: R14.2, U8.8 (SS)
unnamed: R15.2, U8.2 (SYNC/FREQ)
unnamed: R16.2, U8.4 (SLEW)
unnamed: R17.2, U8.3 (SEQ)
unnamed: R18.2, U8.6 (COMP1)
unnamed: R19.2, U8.10 (COMP2)
unnamed: R20.2, R21.1, U8.5 (FB1)
unnamed: R22.2, R23.1, U8.11 (FB2)
UDISP_PWR_EN: R12.2, U8.7 (EN1); also elsewhere on the board
UDISP_SCL: LCD1.62 (SCL_WR), R25.2; also elsewhere on the board
UDISP_SDA: LCD1.63 (SDA), R26.2; also elsewhere on the board
UDISP_~RST: LCD1.67 (RESX), R24.1; also elsewhere on the board

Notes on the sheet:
0 = internal Vdd
Startup: Vpos then Vneg
0 = disable AOI
6.3V
0 = D-PHY
1 = MIPI+I²C
-4.6V
